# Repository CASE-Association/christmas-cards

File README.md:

# christmas-cards
All CASE christmas cards over the years

Go to https://case-association.github.io/christmas-cards/index.html for 2021 version.

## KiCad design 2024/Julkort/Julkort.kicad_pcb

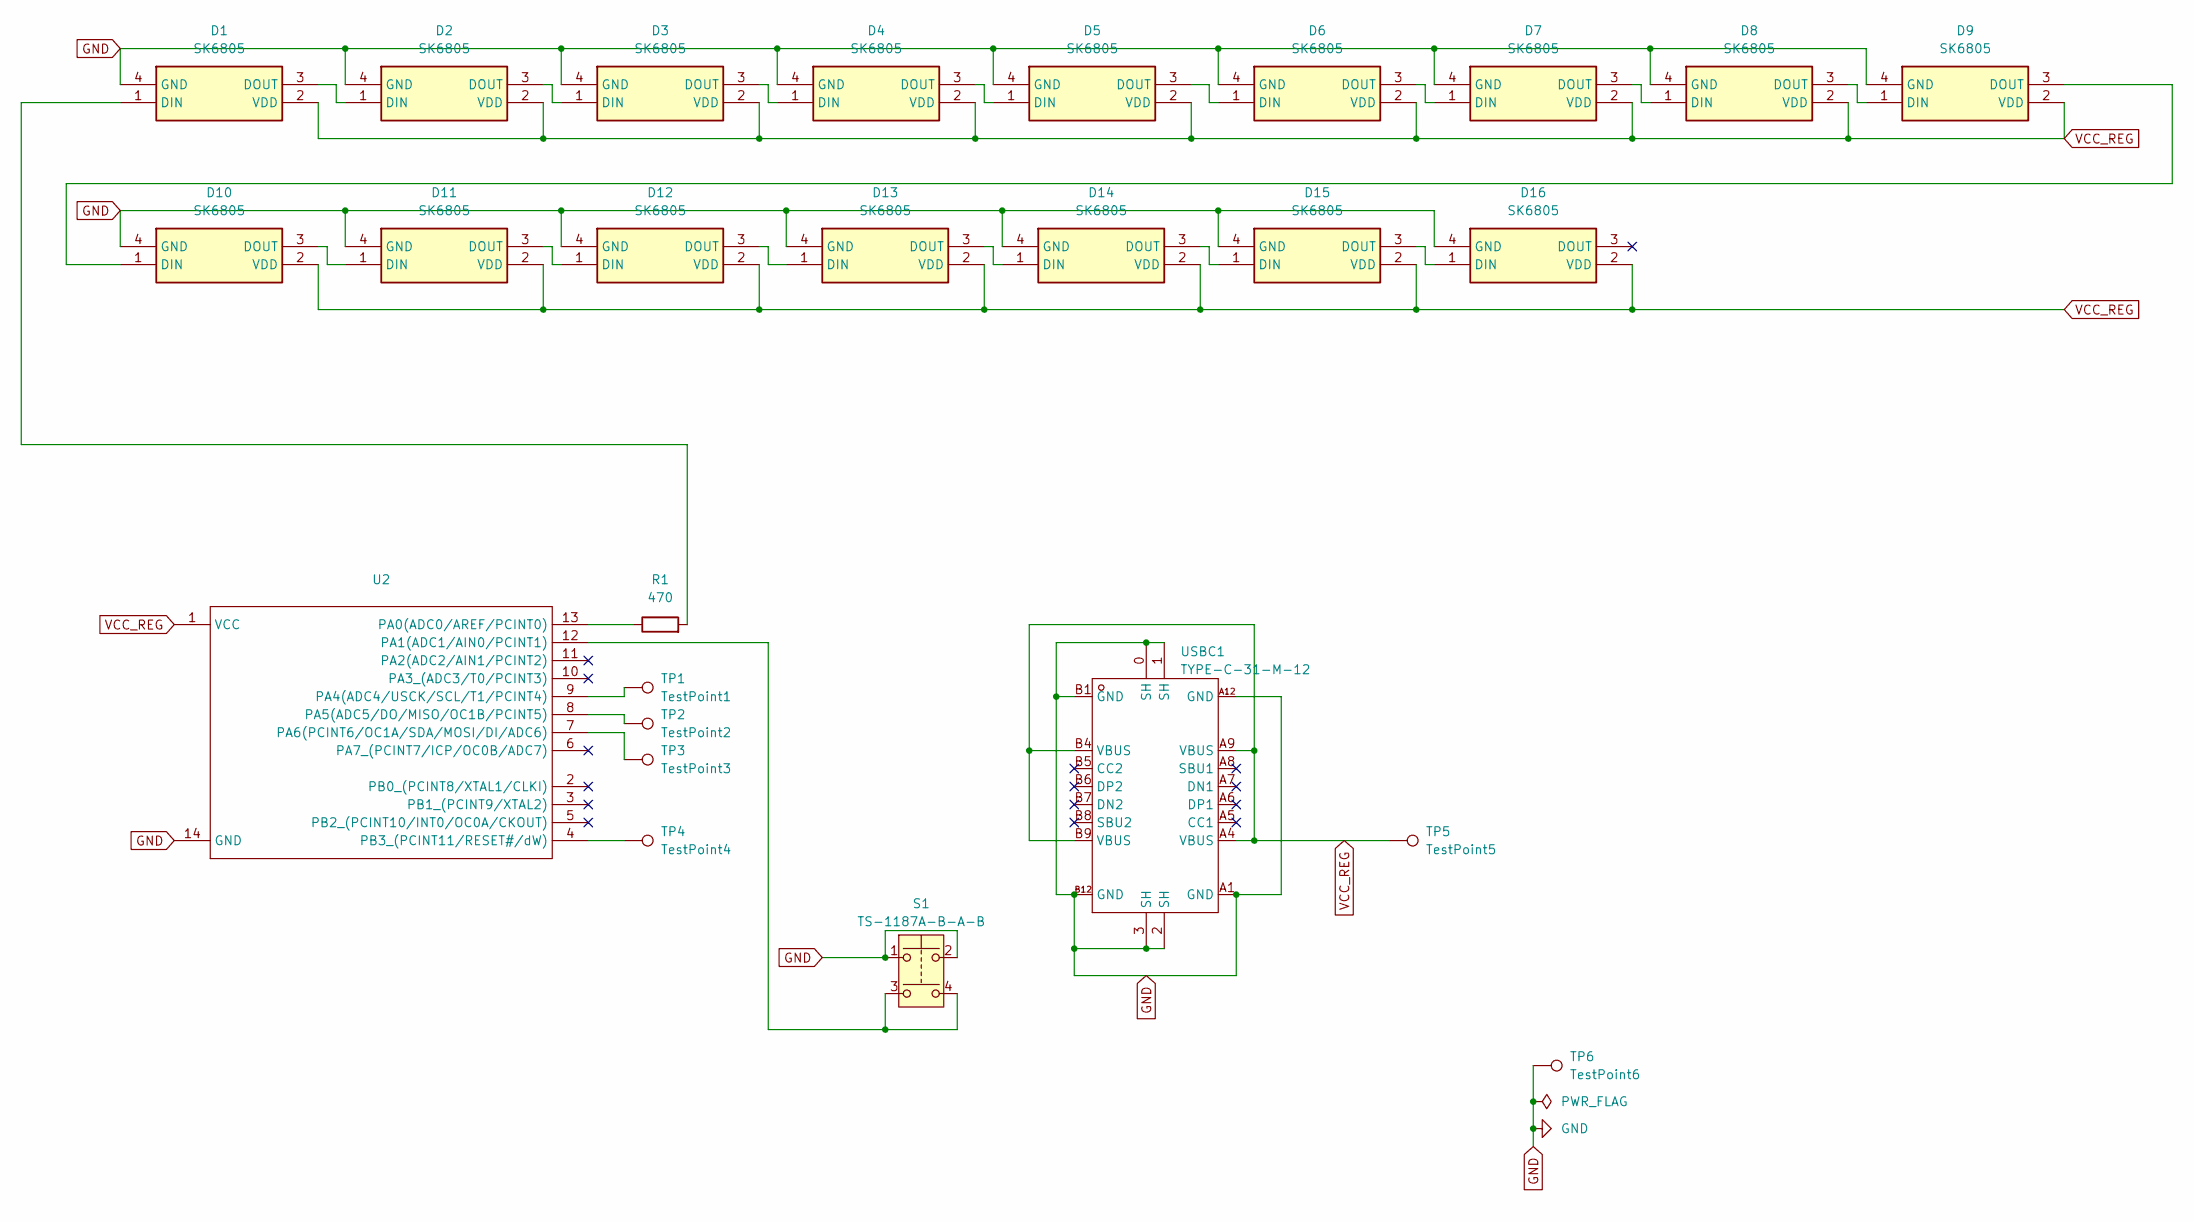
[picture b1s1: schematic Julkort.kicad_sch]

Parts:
D1, D2, D3, D4, D5, D6, D7, D8, D9, D10, D11, D12, D13, D14, D15, D16: SK6805; LED_SK6812_EC15_1.5x1.5mm; Manufacturer_Part_Number SK6805-EC15; LCSC Part # C2909055
R1: 470; R_0603_1608Metric; LCSC Part # C23179
S1: TS-1187A-B-A-B; SW-SMD_4P-L5.1-W5.1-P3.70-LS6.5-TL_H1.5; Manufacturer_Part_Number TS-1187A-B-A-B; LCSC Part # C412370
TP1: TestPoint1; TestPoint_Pad_D1.5mm
TP2: TestPoint2; TestPoint_Pad_D1.5mm
TP3: TestPoint3; TestPoint_Pad_D1.5mm
TP4: TestPoint4; TestPoint_Pad_D1.5mm
TP5: TestPoint5; TestPoint_Pad_D1.5mm
TP6: TestPoint6; TestPoint_Pad_D1.5mm
U2: SOP-14_L8.6-W3.9-P1.27-LS6.0-BL; Manufacturer Part ATTINY44A-SSUR; LCSC Part Name ATTINY44A-SSUR
USBC1: TYPE-C-31-M-12; USB-C_SMD-TYPE-C-31-M-12; Manufacturer Part TYPE-C-31-M-12; LCSC Part Name Type-C 母

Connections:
GND: D1.4 (GND), D2.4 (GND), D3.4 (GND), D4.4 (GND), D5.4 (GND), D6.4 (GND), D7.4 (GND), D8.4 (GND), D9.4 (GND), D10.4 (GND), D11.4 (GND), D12.4 (GND), D13.4 (GND), D14.4 (GND), D15.4 (GND), D16.4 (GND), S1.1, S1.2, TP6.1, U2.14 (GND), USBC1.0 (SH), USBC1.1 (SH), USBC1.2 (SH), USBC1.3 (SH), USBC1.A1 (GND), USBC1.A12 (GND), USBC1.B1 (GND), USBC1.B12 (GND)
unnamed: D1.1 (DIN), R1.2
unnamed: D1.3 (DOUT), D2.1 (DIN)
unnamed: D2.3 (DOUT), D3.1 (DIN)
unnamed: D3.3 (DOUT), D4.1 (DIN)
unnamed: D4.3 (DOUT), D5.1 (DIN)
unnamed: D5.3 (DOUT), D6.1 (DIN)
unnamed: D6.3 (DOUT), D7.1 (DIN)
unnamed: D7.3 (DOUT), D8.1 (DIN)
unnamed: D8.3 (DOUT), D9.1 (DIN)
unnamed: D9.3 (DOUT), D10.1 (DIN)
unnamed: D10.3 (DOUT), D11.1 (DIN)
unnamed: D11.3 (DOUT), D12.1 (DIN)
unnamed: D12.3 (DOUT), D13.1 (DIN)
unnamed: D13.3 (DOUT), D14.1 (DIN)
unnamed: D14.3 (DOUT), D15.1 (DIN)
unnamed: D15.3 (DOUT), D16.1 (DIN)
unnamed: R1.1, U2.13 (PA0(ADC0/AREF/PCINT0))
unnamed: S1.3, S1.4, U2.12 (PA1(ADC1/AIN0/PCINT1))
unnamed: TP1.1, U2.9 (PA4(ADC4/USCK/SCL/T1/PCINT4))
unnamed: TP2.1, U2.8 (PA5(ADC5/DO/MISO/OC1B/PCINT5))
unnamed: TP3.1, U2.7 (PA6(PCINT6/OC1A/SDA/MOSI/DI/ADC6))
unnamed: TP4.1, U2.4 (PB3_(PCINT11/RESET#/dW))
VCC_REG: D1.2 (VDD), D2.2 (VDD), D3.2 (VDD), D4.2 (VDD), D5.2 (VDD), D6.2 (VDD), D7.2 (VDD), D8.2 (VDD), D9.2 (VDD), D10.2 (VDD), D11.2 (VDD), D12.2 (VDD), D13.2 (VDD), D14.2 (VDD), D15.2 (VDD), D16.2 (VDD), TP5.1, U2.1 (VCC), USBC1.A4 (VBUS), USBC1.A9 (VBUS), USBC1.B4 (VBUS), USBC1.B9 (VBUS)

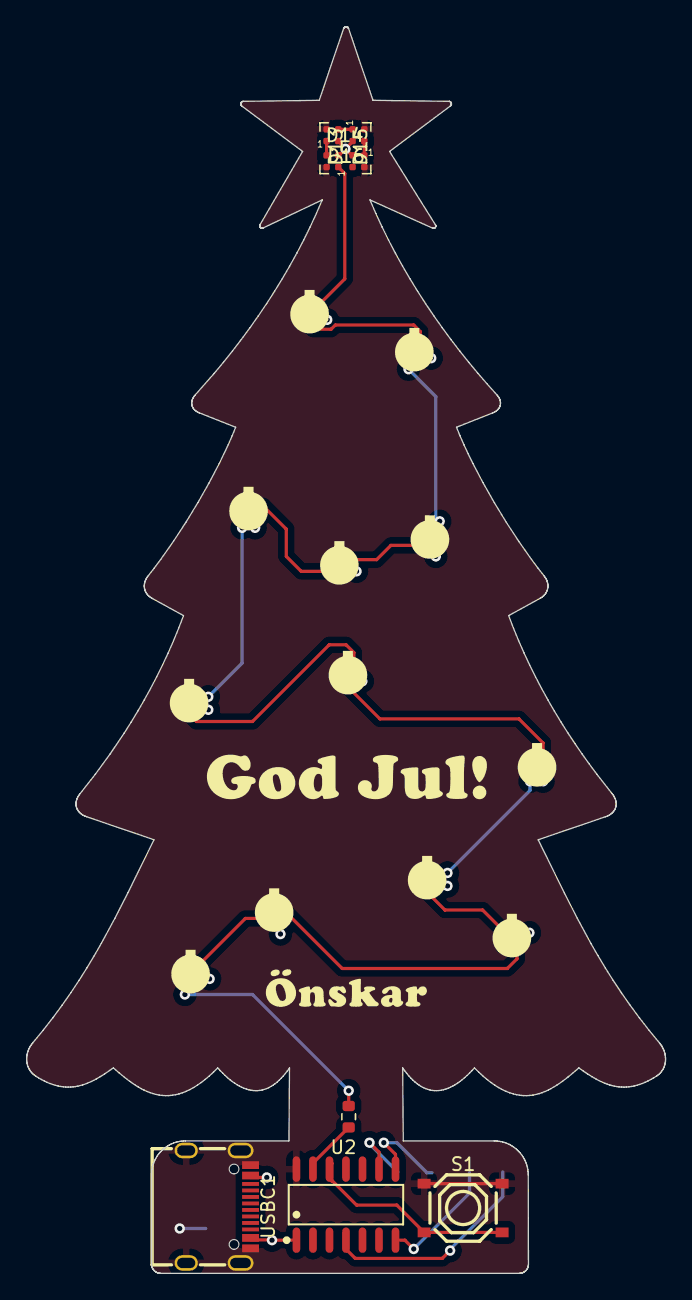
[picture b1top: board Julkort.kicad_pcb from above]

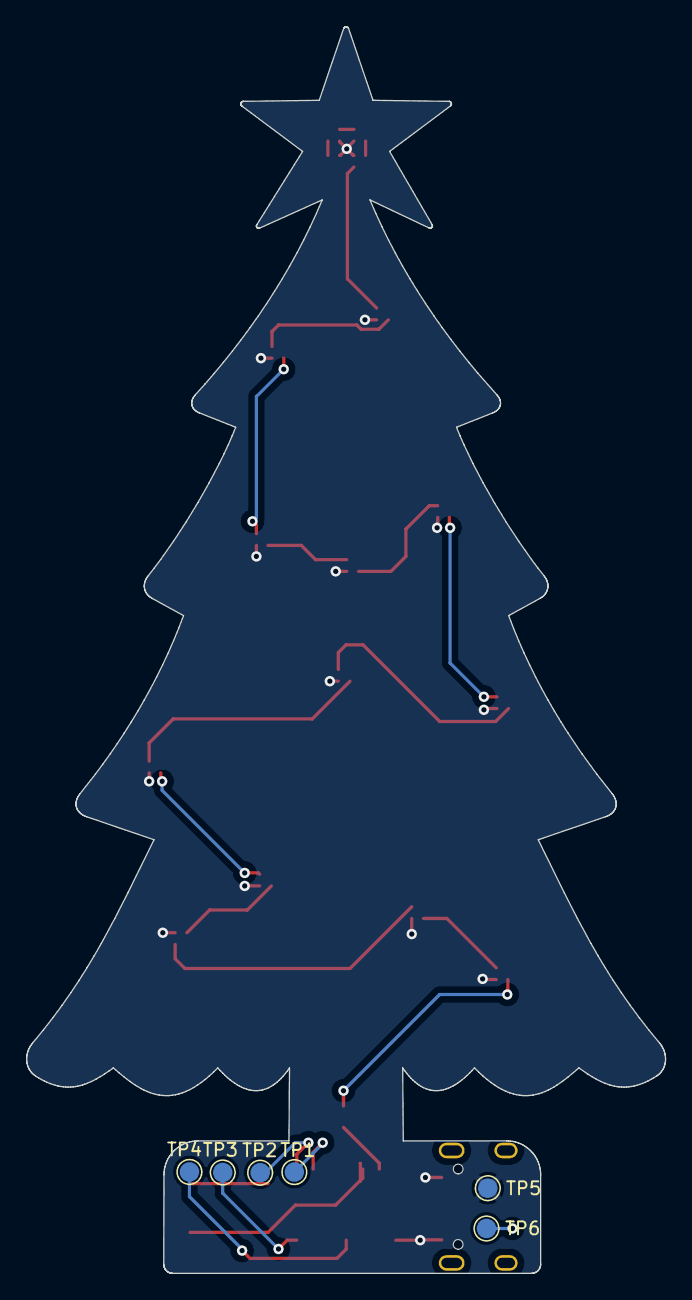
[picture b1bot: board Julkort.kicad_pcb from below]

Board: 2 copper layers, 49.1 x 95.9 mm, 26 parts (6 on the bottom side), 24 nets.

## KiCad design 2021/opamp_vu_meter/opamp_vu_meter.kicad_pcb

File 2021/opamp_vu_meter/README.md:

## The 2021 version, with lights that blink with music!

Go to https://case-association.github.io/christmas-cards/index.html for interactive BOM.

[Eschema](https://github.com/CASE-Association/christmas-cards/raw/main/2021/opamp_vu_meter/eschema.pdf)

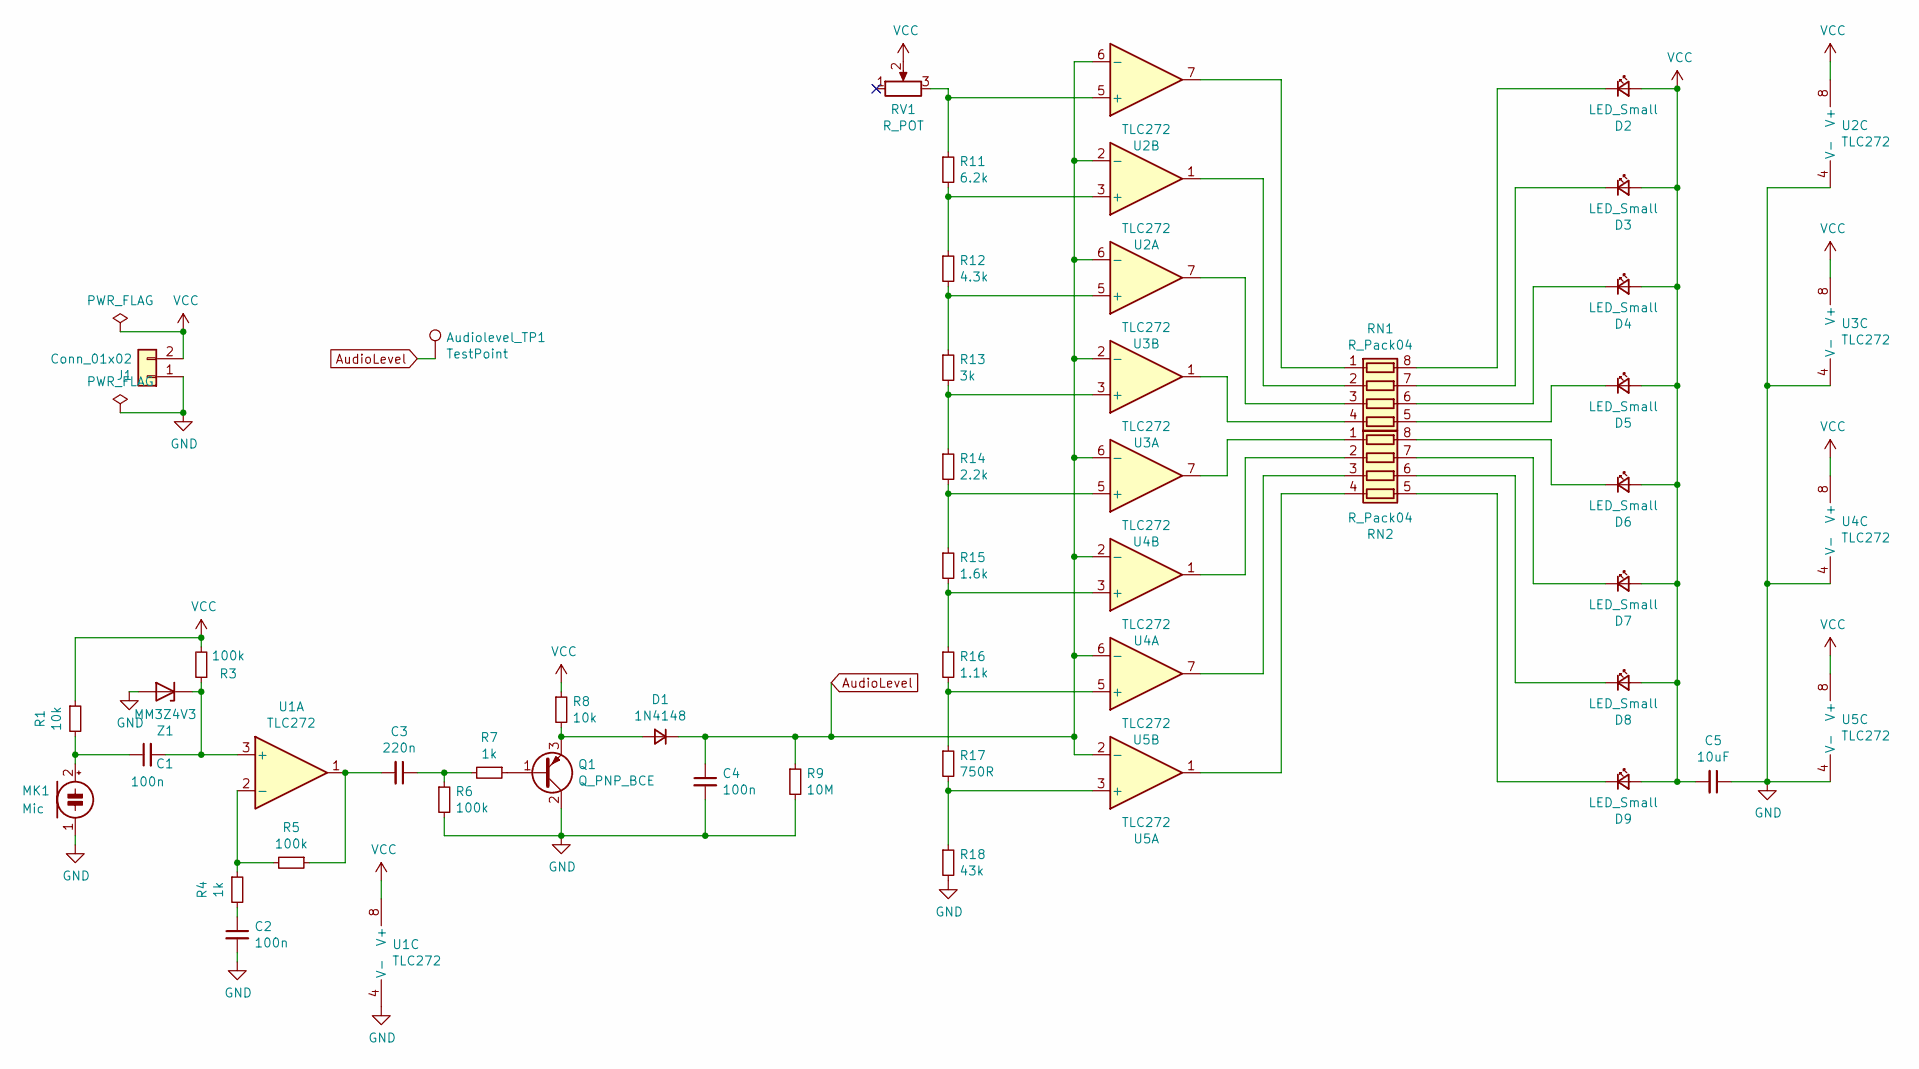
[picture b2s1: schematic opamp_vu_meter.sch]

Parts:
Audiolevel_TP1: TestPoint; TestPoint_Pad_D1.5mm
C1, C2, C4: 100n; C_0805_2012Metric_Pad1.18x1.45mm_HandSolder
C3: 220n; C_0805_2012Metric_Pad1.18x1.45mm_HandSolder
C5: 10uF; C_0805_2012Metric_Pad1.18x1.45mm_HandSolder
D1: 1N4148; D_SOD-123
D2, D3, D4, D5, D6, D7, D8, D9: LED_Small; LED_0805_2012Metric_Pad1.15x1.40mm_HandSolder
J1: Conn_01x02; TerminalBlock_Phoenix_MKDS-1,5-2-5.08_1x02_P5.08mm_Horizont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
MK1: Mic; CMA4544PFW
Q1: Q_PNP_BCE; SOT-23
R1, R8: 10k; R_0805_2012Metric_Pad1.20x1.40mm_HandSolder
R3, R5, R6: 100k; R_0805_2012Metric_Pad1.20x1.40mm_HandSolder
R4, R7: 1k; R_0805_2012Metric_Pad1.20x1.40mm_HandSolder
R9: 10M; R_0805_2012Metric_Pad1.20x1.40mm_HandSolder
R11: 6.2k; R_0805_2012Metric_Pad1.20x1.40mm_HandSolder
R12: 4.3k; R_0805_2012Metric_Pad1.20x1.40mm_HandSolder
R13: 3k; R_0805_2012Metric_Pad1.20x1.40mm_HandSolder
R14: 2.2k; R_0805_2012Metric_Pad1.20x1.40mm_HandSolder
R15: 1.6k; R_0805_2012Metric_Pad1.20x1.40mm_HandSolder
R16: 1.1k; R_0805_2012Metric_Pad1.20x1.40mm_HandSolder
R17: 750R; R_0805_2012Metric_Pad1.20x1.40mm_HandSolder
R18: 43k; R_0805_2012Metric_Pad1.20x1.40mm_HandSolder
RN1, RN2: R_Pack04; R_Array_Convex_4x1206
RV1: R_POT; Potentiometer_Bourns_TC33X_Vertical
U1, U2, U3, U4, U5: TLC272; SOIC-8_3.9x4.9mm_P1.27mm
Z1: MM3Z4V3; D_SOD-123F

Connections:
AudioLevel: Audiolevel_TP1.1, C4.1, D1.1 (K), R9.1, U2.2 (-), U2.6 (-), U3.2 (-), U3.6 (-), U4.2 (-), U4.6 (-), U5.2 (-), U5.6 (-)
GND: C2.2, C4.2, C5.1, J1.1, MK1.1 (-), Q1.2 (C), R6.2, R9.2, R18.2, U1.4 (V-), U2.4 (V-), U3.4 (V-), U4.4 (V-), U5.4 (V-), Z1.2 (A)
unnamed: C1.1, MK1.2 (+), R1.2
unnamed: C1.2, R3.1, U1.3 (+), Z1.1 (K)
unnamed: C2.1, R4.2
unnamed: C3.1, R6.1, R7.2
unnamed: C3.2, R5.1, U1.1
unnamed: D1.2 (A), Q1.3 (E), R8.2
unnamed: D2.1 (K), RN1.8 (R1.2)
unnamed: D3.1 (K), RN1.7 (R2.2)
unnamed: D4.1 (K), RN1.6 (R3.2)
unnamed: D5.1 (K), RN1.5 (R4.2)
unnamed: D6.1 (K), RN2.8 (R1.2)
unnamed: D7.1 (K), RN2.7 (R2.2)
unnamed: D8.1 (K), RN2.6 (R3.2)
unnamed: D9.1 (K), RN2.5 (R4.2)
unnamed: Q1.1 (B), R7.1
unnamed: R4.1, R5.2, U1.2 (-)
unnamed: R11.1, RV1.3, U2.5 (+)
unnamed: R11.2, R12.1, U2.3 (+)
unnamed: R12.2, R13.1, U3.5 (+)
unnamed: R13.2, R14.1, U3.3 (+)
unnamed: R14.2, R15.1, U4.5 (+)
unnamed: R15.2, R16.1, U4.3 (+)
unnamed: R16.2, R17.1, U5.5 (+)
unnamed: R17.2, R18.1, U5.3 (+)
unnamed: RN1.1 (R1.1), U2.7
unnamed: RN1.2 (R2.1), U2.1
unnamed: RN1.3 (R3.1), U3.7
unnamed: RN1.4 (R4.1), U3.1
unnamed: RN2.1 (R1.1), U4.7
unnamed: RN2.2 (R2.1), U4.1
unnamed: RN2.3 (R3.1), U5.7
unnamed: RN2.4 (R4.1), U5.1
VCC: C5.2, D2.2 (A), D3.2 (A), D4.2 (A), D5.2 (A), D6.2 (A), D7.2 (A), D8.2 (A), D9.2 (A), J1.2, R1.1, R3.2, R8.1, RV1.2, U1.8 (V+), U2.8 (V+), U3.8 (V+), U4.8 (V+), U5.8 (V+)

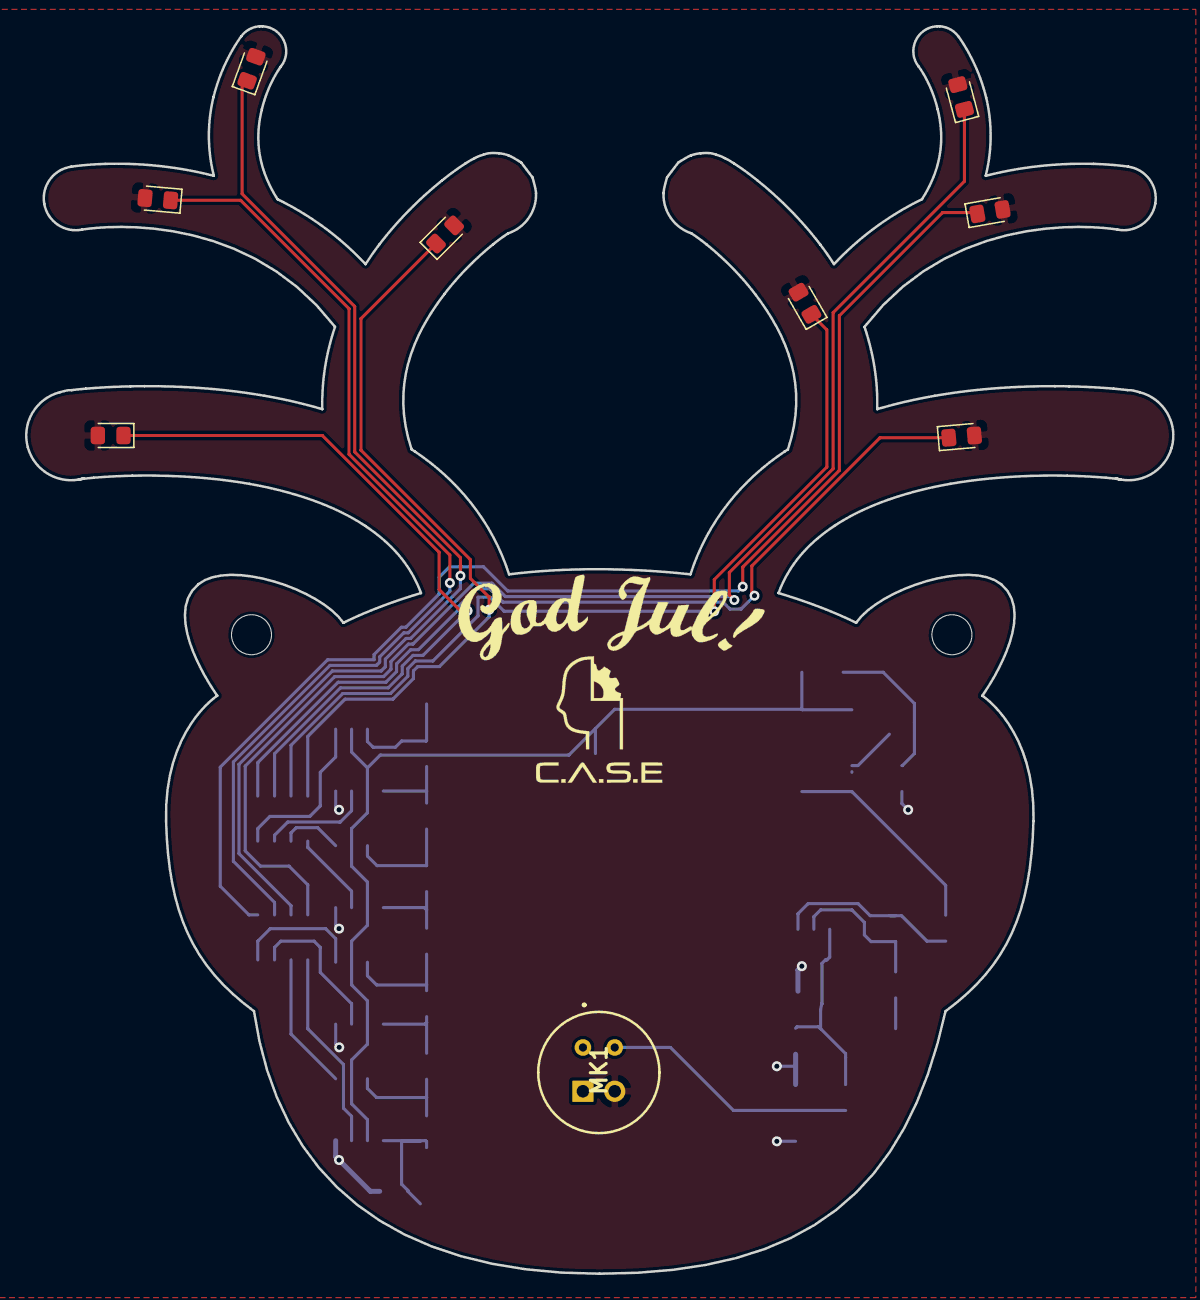
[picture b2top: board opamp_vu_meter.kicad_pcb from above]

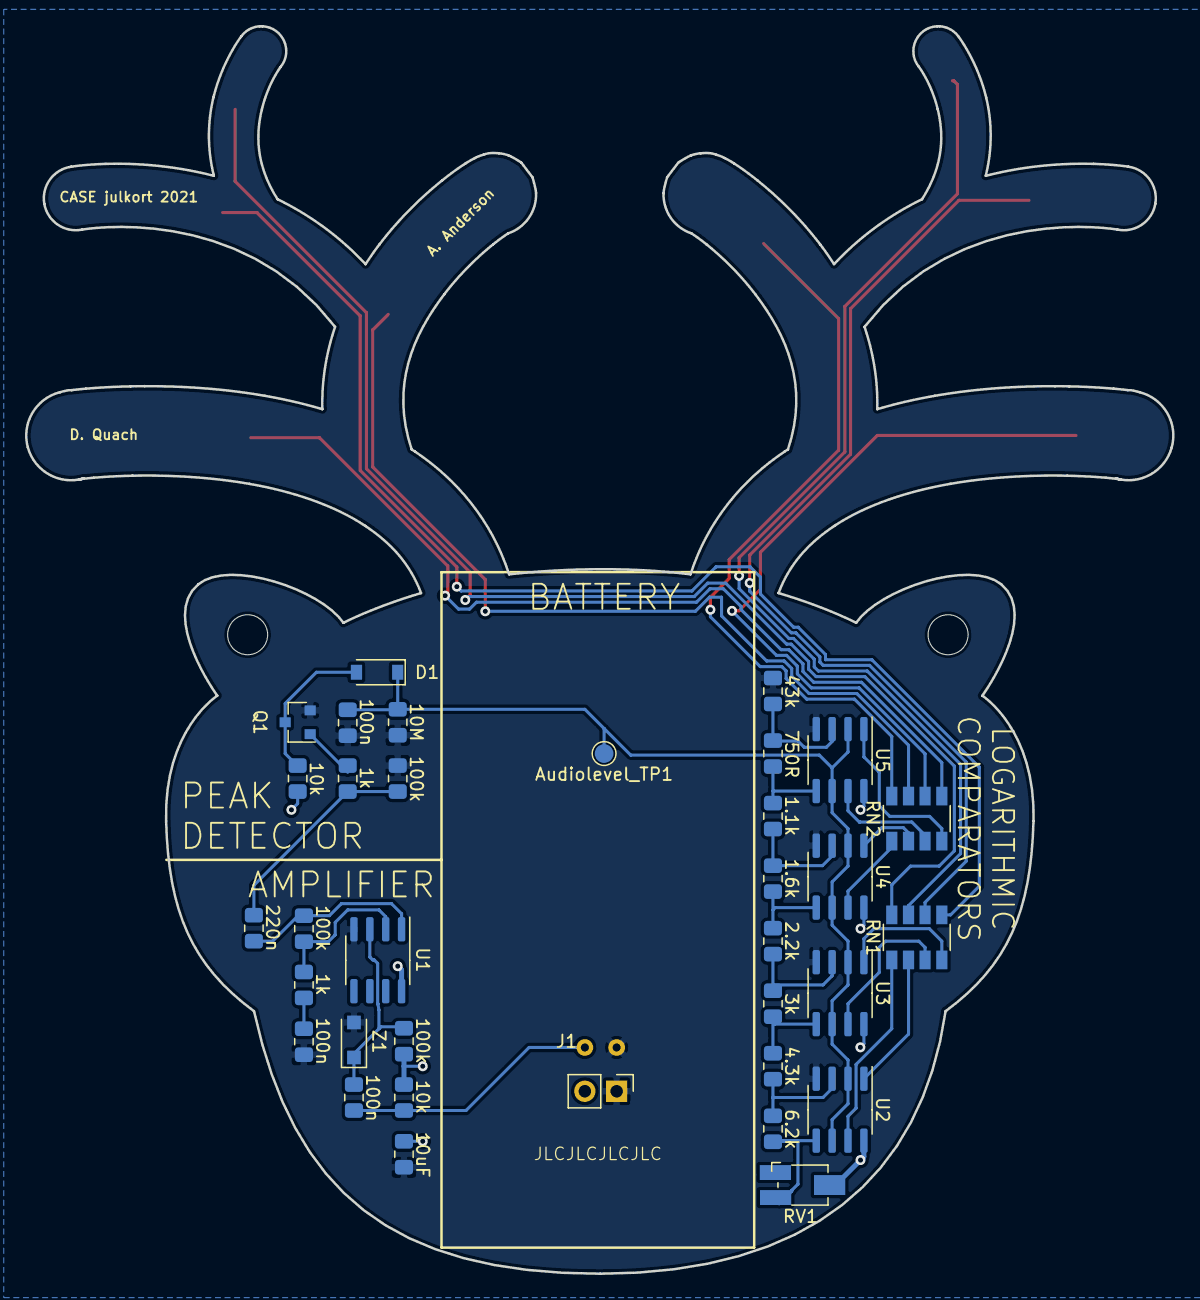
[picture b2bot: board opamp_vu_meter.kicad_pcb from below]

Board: 2 copper layers, 91.7 x 99.7 mm, 43 parts (34 on the bottom side), 35 nets.

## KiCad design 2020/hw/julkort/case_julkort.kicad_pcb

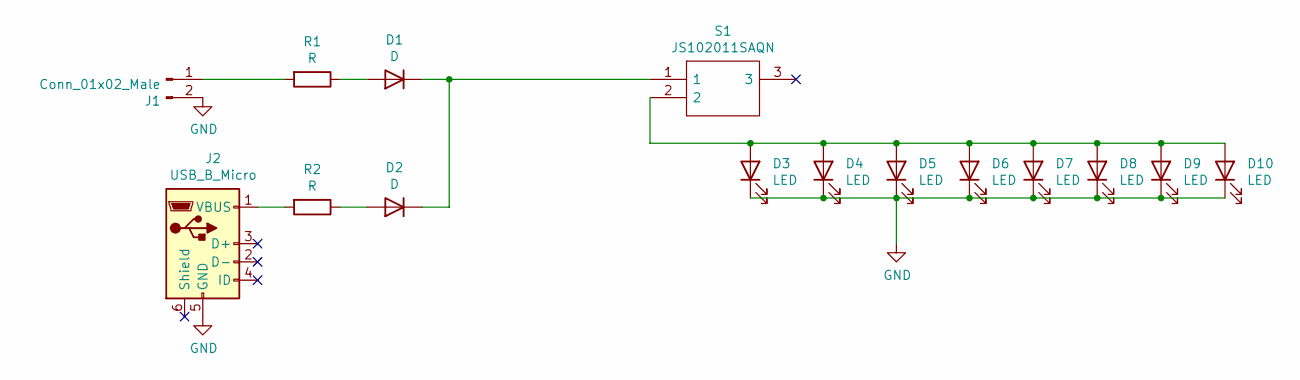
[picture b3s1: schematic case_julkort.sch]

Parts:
D1, D2: D; D_SOD-123
D3, D4, D5, D6, D7, D8, D9, D10: LED; LED_0805_2012Metric_Pad1.15x1.40mm_HandSolder
J1: Conn_01x02_Male; 2xAA_RS_PRO
J2: USB_B_Micro; USB_Micro-B_Molex-105017-0001
R1: R; R_0805_2012Metric_Pad1.15x1.40mm_HandSolder
R2: R; R_2512_6332Metric_Pad1.52x3.35mm_HandSolder
S1: JS102011SAQN; Mouser Part Number 611-JS102011SAQN

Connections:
GND: D3.1 (K), D4.1 (K), D5.1 (K), D6.1 (K), D7.1 (K), D8.1 (K), D9.1 (K), D10.1 (K), J1.2, J2.5 (GND)
unnamed: D1.1 (K), D2.1 (K), S1.1
unnamed: D1.2 (A), R1.1
unnamed: D2.2 (A), R2.1
unnamed: D3.2 (A), D4.2 (A), D5.2 (A), D6.2 (A), D7.2 (A), D8.2 (A), D9.2 (A), D10.2 (A), S1.2
unnamed: J1.1, R1.2
unnamed: J2.1 (VBUS), R2.2

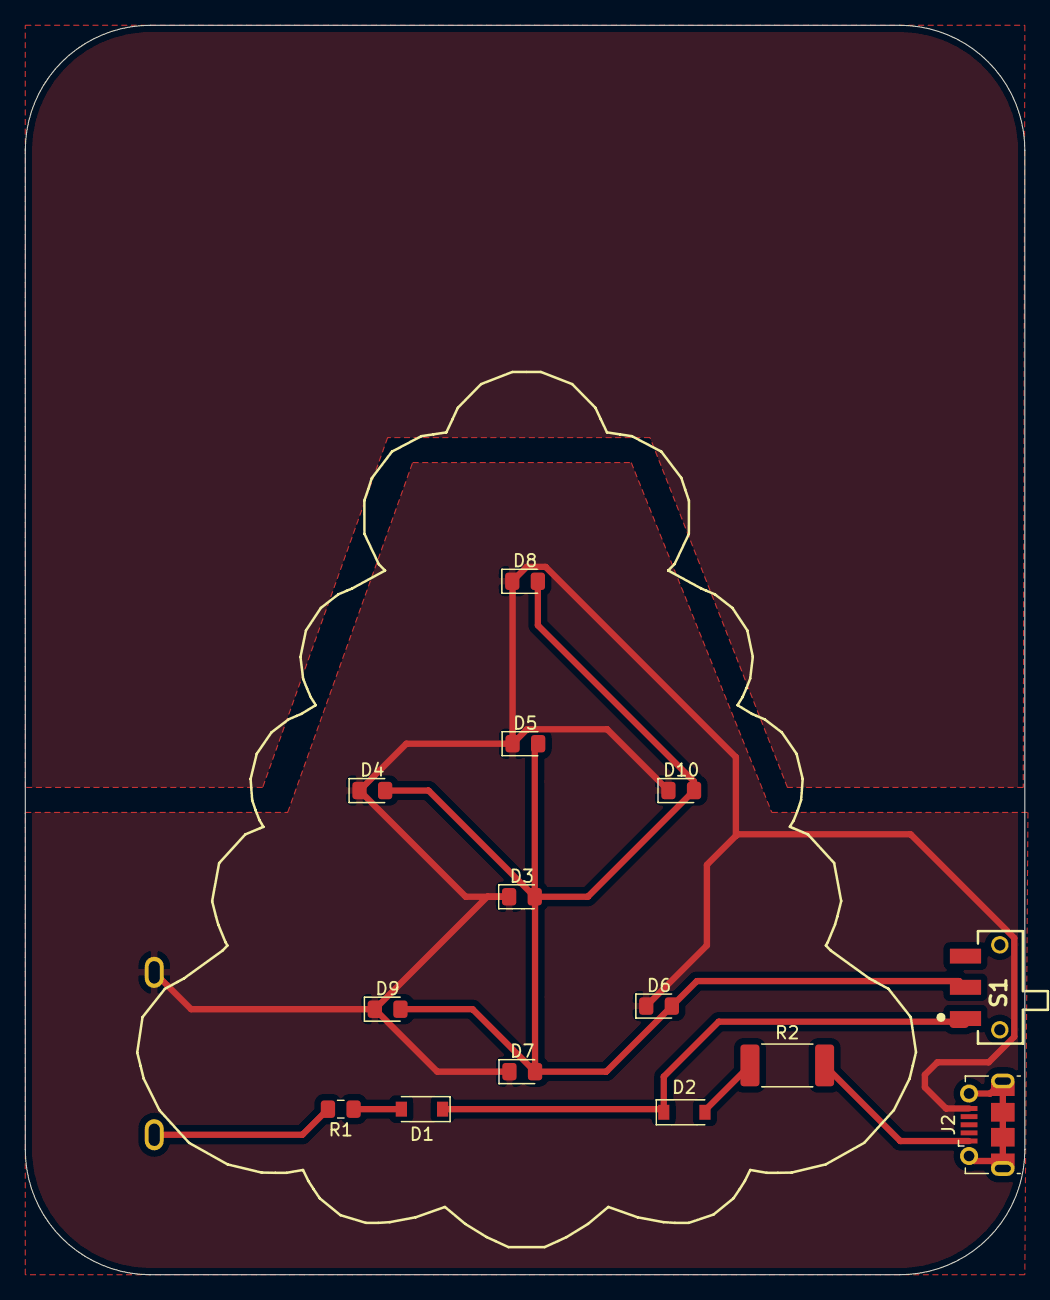
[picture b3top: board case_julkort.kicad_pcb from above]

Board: 2 copper layers, 80.0 x 100.0 mm, 15 parts (1 on the bottom side), 7 nets.

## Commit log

2021-01-22 Added 2019
2021-01-24 Structure for 2020
2021-01-24 added kicad files
2021-03-17 Added hyperlink
2021-11-04 add 2021 proto
2021-11-05 Changed outline shape and component placement
2021-11-13 Final version (hopefully)
2021-12-09 Minor revision with zener to stabilize
2021-12-09 Rotate one component
2021-12-17 Create LICENSE
2021-12-17 Updated peak detector values
2021-12-18 Updated eschema.pdf
2022-01-28 Add media
2024-11-22 USB-C 2024 first version
2024-11-26 2024 v1
2024-11-26 Blankt kort + starterkit för workshop
2024-11-29 Byte av atmega44-footprint
2024-12-17 first code for christmas cards, button compatability to be added
2025-05-19 2024 ATtiny Code
